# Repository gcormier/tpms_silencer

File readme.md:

# tpms_silencer
Open hardware that supports ASK/FSK transmit on 315/433MHz ISM bands. General point is to spoof TPMS sensors but
it could be used for any type of ASK/FSK transmittion on bands supported by the IC.

Big thanks to <a href="https://github.com/merbanan/rtl_433">rtl_433</a> project, wouldn't exist without their hard work for
decoding the TPMS in the first place.

## Availability
Boards are for sale https://www.tindie.com/products/gcormier/tpms-silencer/

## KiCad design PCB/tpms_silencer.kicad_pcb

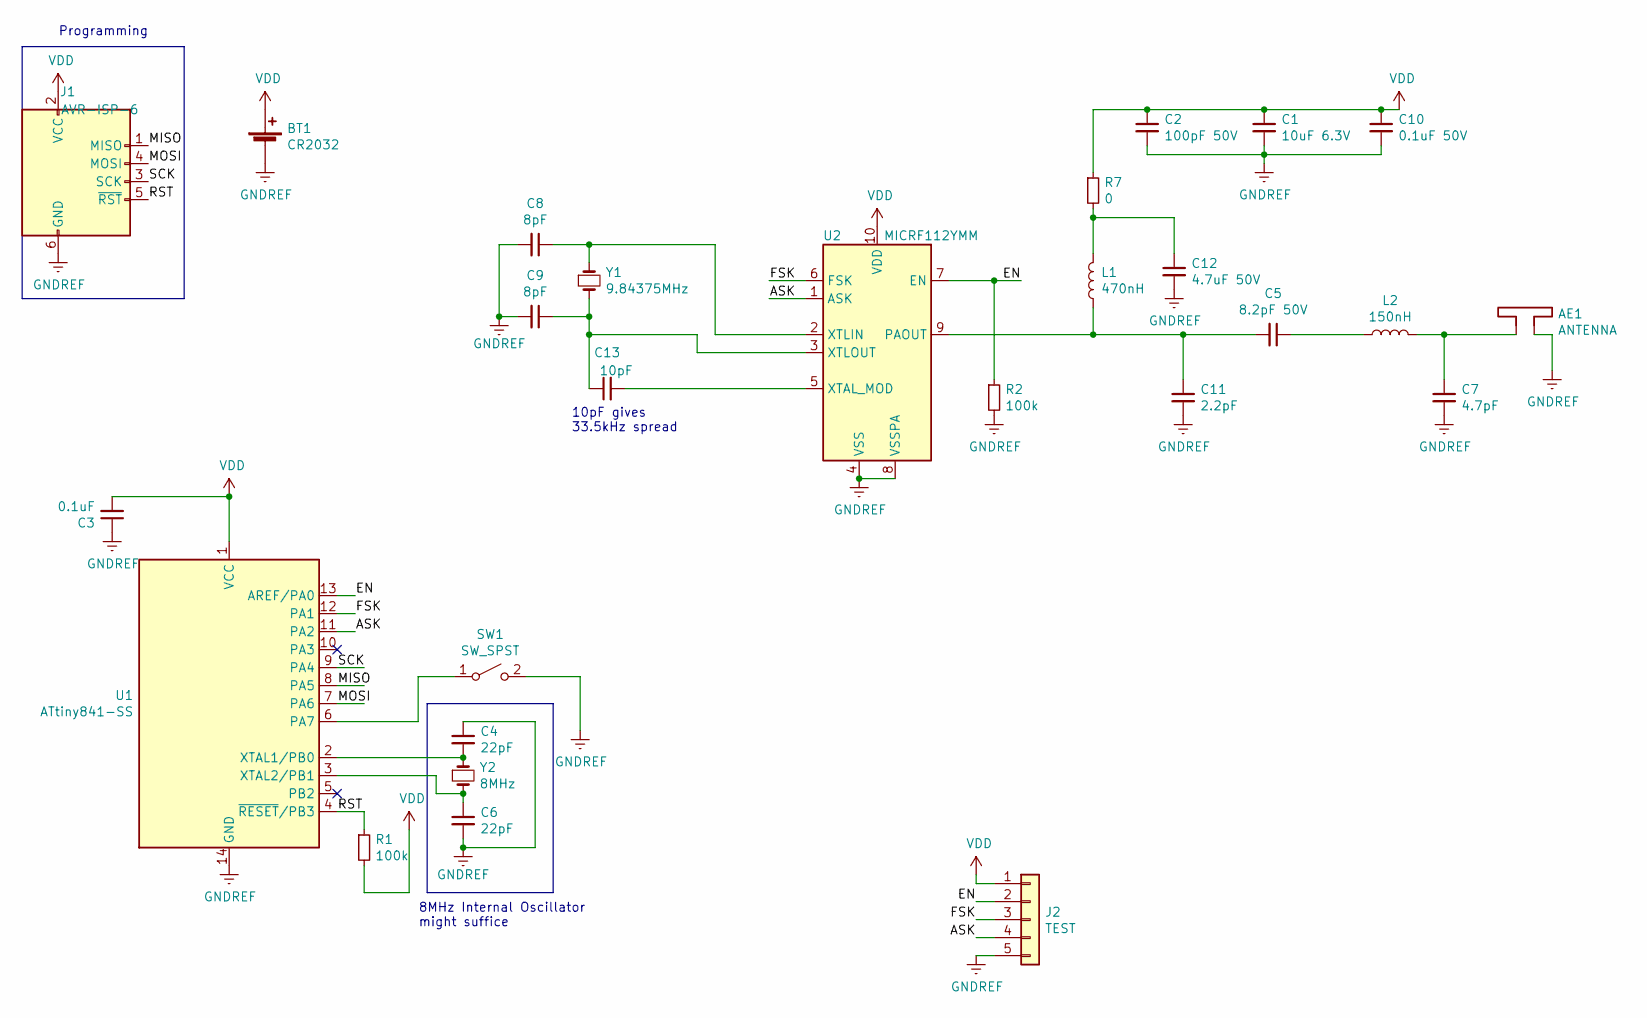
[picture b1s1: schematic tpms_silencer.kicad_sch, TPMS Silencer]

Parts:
AE1: ANTENNA; 315MHz Antenna
BT1: CR2032; BatteryHolder_Keystone_3034_1x20mm
C1: 10uF 6.3V; C_0805_2012Metric
C2: 100pF 50V; C_0805_2012Metric
C3: 0.1uF; C_0805_2012Metric
C4, C6: 22pF; C_0805_2012Metric
C5: 8.2pF 50V; C_0805_2012Metric
C7: 4.7pF; C_0805_2012Metric
C8, C9: 8pF; C_0805_2012Metric
C10: 0.1uF 50V; C_0805_2012Metric
C11: 2.2pF; C_0805_2012Metric
C12: 4.7uF 50V; C_0805_2012Metric
C13: 10pF; C_0805_2012Metric
J1: AVR-ISP-6; AVR-SMD-Programming-Header
J2: TEST; PinHeader_1x05_P2.54mm_Horizontal
L1: 470nH; L_0805_2012Metric
L2: 150nH; L_0805_2012Metric
R1, R2: 100k; R_0805_2012Metric
R7: 0; R_0805_2012Metric
SW1: SW_SPST; SW_SPST_PTS645
U1: ATtiny841-SS; SOIC-14_3.9x8.7mm_P1.27mm
U2: MICRF112YMM; MSOP-10_3x3mm_P0.5mm
Y1: 9.84375MHz; Crystal_SMD_HC49-SD
Y2: 8MHz; Crystal_SMD_TXC_7A-2Pin_5x3.2mm

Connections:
/ASK: J2.4, U1.11 (PA2), U2.1 (ASK)
/EN: J2.2, R2.1, U1.13 (AREF/PA0), U2.7 (EN)
/FSK: J2.3, U1.12 (PA1), U2.6 (FSK)
/MISO: J1.1 (MISO), U1.8 (PA5)
/MOSI: J1.4 (MOSI), U1.7 (PA6)
/RST: J1.5 (~RST), R1.1, U1.4 (~RESET/PB3)
/SCK: J1.3 (SCK), U1.9 (PA4)
GNDREF: AE1.2, BT1.2 (-), C1.2, C2.2, C3.1, C4.1, C6.2, C7.2, C8.2, C9.2, C10.2, C11.2, C12.2, J1.6 (GND), J2.5, R2.2, SW1.2 (B), U1.14 (GND), U2.4 (VSS), U2.8 (VSSPA)
unnamed: AE1.1, C7.1, L2.2
unnamed: C4.2, U1.2 (XTAL1/PB0), Y2.1
unnamed: C5.1, L2.1
unnamed: C6.1, U1.3 (XTAL2/PB1), Y2.2
unnamed: C8.1, U2.2 (XTLIN), Y1.1
unnamed: C5.2, C11.1, L1.1, U2.9 (PAOUT)
unnamed: C12.1, L1.2, R7.2
unnamed: C9.1, C13.1, U2.3 (XTLOUT), Y1.2
unnamed: C13.2, U2.5 (XTAL_MOD)
unnamed: SW1.1 (A), U1.6 (PA7)
VDD: BT1.1 (+), C1.1, C2.1, C3.2, C10.1, J1.2 (VCC), J2.1, R1.2, R7.1, U1.1 (VCC), U2.10 (VDD)

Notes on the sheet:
10pF gives 33.5kHz spread
8MHz Internal Oscillator might suffice
Programming

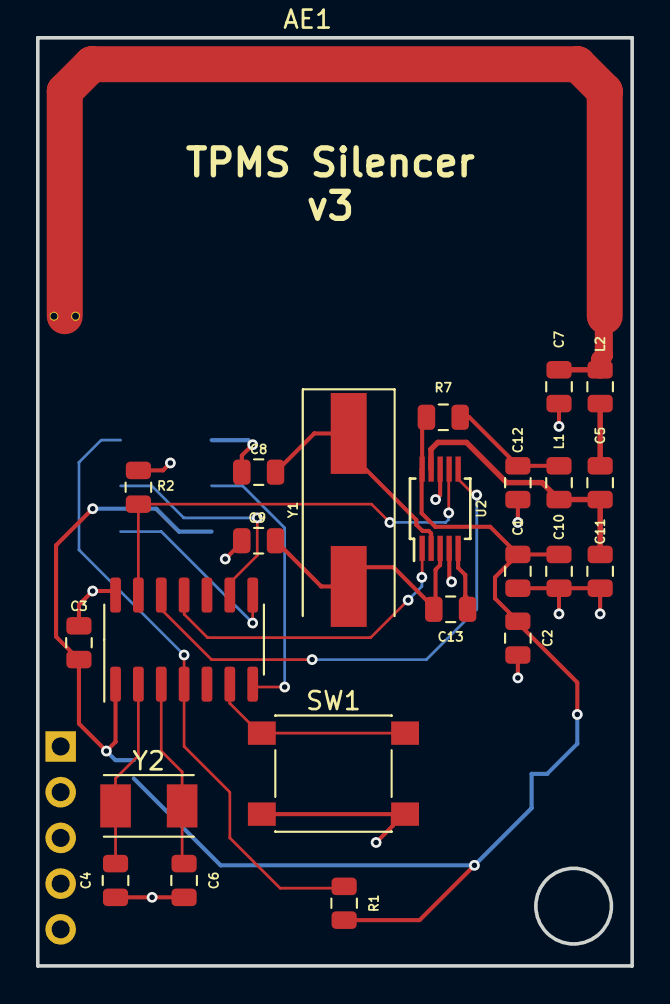
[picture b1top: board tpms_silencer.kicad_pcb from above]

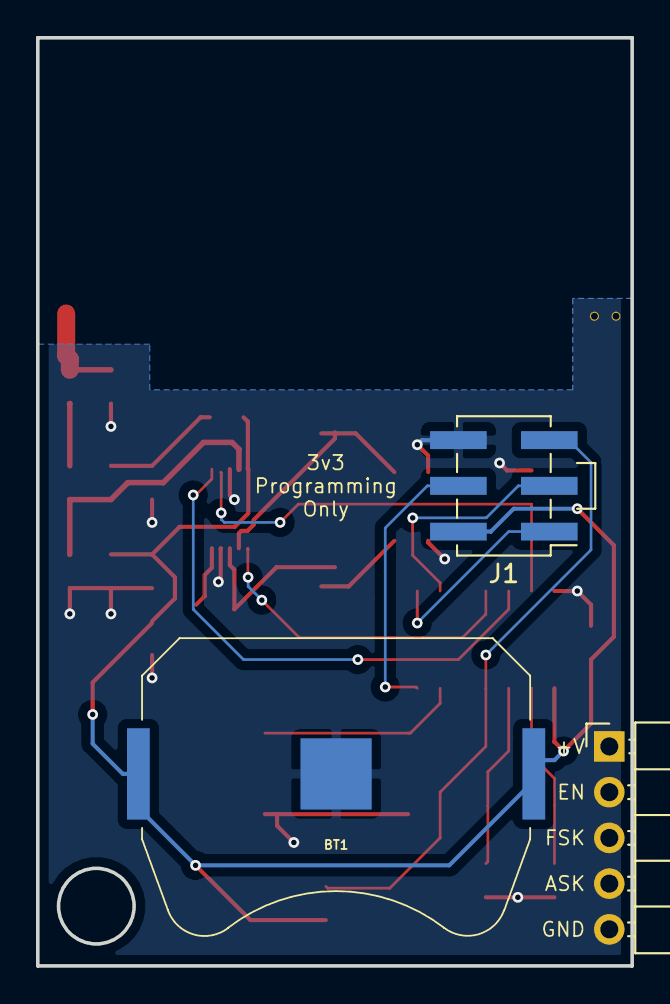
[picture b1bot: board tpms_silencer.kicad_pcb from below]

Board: 2 copper layers, 33.0 x 51.6 mm, 27 parts (3 on the bottom side), 19 nets.

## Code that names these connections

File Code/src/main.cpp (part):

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BACKOFF will double the retransmit period each time until MAX_LIMIT.
*/

#define PIN_EN     A0  // PA0, Pin 13, Arduino 10
#define PIN_FSK    A1 // PA1, Pin 12, Arduino 9
#define PIN_ASK    A2 // PA2, Pin 11, Arduino 8
#define PIN_BUTTON A7 // PA7, Pin 6, PCINT7
#define INTERRUPT_PIN PCINT7 // interrupt for PA7

#define PERIODIC_TX // periodic retransmissions. disable for button-press tx only
//#define BACKOFF    // double transmit period everytime? disable to have a fixed period retrans.
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  // find more in power.h

  pinMode(PIN_EN, OUTPUT);
  pinMode(PIN_FSK, OUTPUT);
  pinMode(PIN_ASK, OUTPUT);
  pinMode(PIN_BUTTON, INPUT_PULLUP);
  
#ifdef PERIODIC_TX
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
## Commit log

2018-11-12 updated ignore
2018-11-13 readme
2018-11-13 Change programming header, comments on capacitor, v2 layout, hole for mounting in enclosure
2018-12-03 V2 - sent for fab.
2019-01-12 latest changes
2019-03-25 Prep for release.
2019-03-25 Release
2019-03-25 image
2019-03-25 formatting
2019-03-25 rotate
2019-03-25 size
2019-03-26 test
2019-04-03 notes for 433mhz parts
2020-04-17 leaf
2020-11-22 convert to platformio
2020-11-23 add test points and update annotation to match MICRF112-315-EV
2021-11-21 working on green unit
2021-11-21 Backoff algorithm
2021-11-21 backoff implemented
2021-11-21 move watchdog setup to setup
2021-11-21 little cleanups
2021-11-21 backoff to max
2021-11-21 compact packets, poweroff timer1 between packets
2021-11-21 loop over packets now
2021-11-23 various refinements
2021-11-23 further refinements
2021-11-23 comments mostly
2021-11-23 remove support for hw-modification
2021-11-24 update to kicad v6
